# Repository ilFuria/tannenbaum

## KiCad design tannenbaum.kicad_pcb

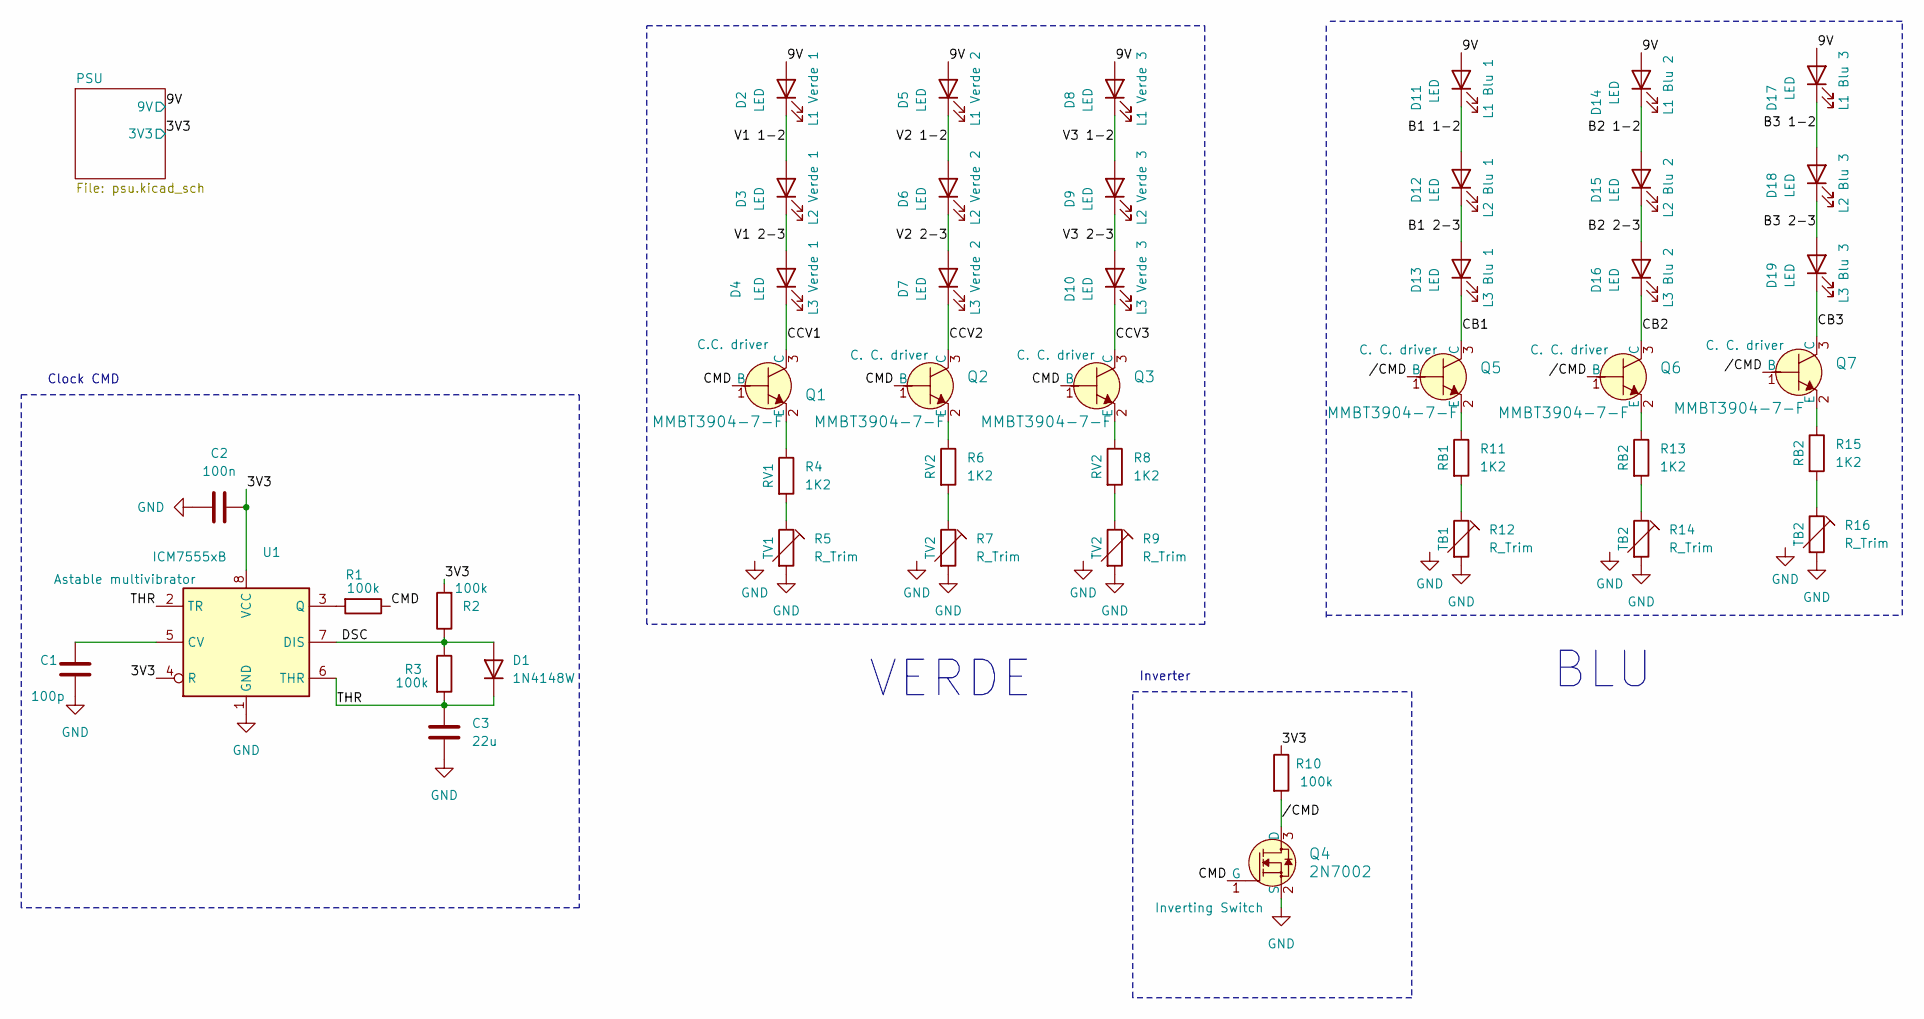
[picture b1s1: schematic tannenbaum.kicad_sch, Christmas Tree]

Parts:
C1: 100p; C_0603_1608Metric
C2: 100n; C_0805_2012Metric
C3: 22u; CP_Elec_6.3x5.7
D1: 1N4148W; D_SOD-123
D2, D3, D4, D5, D6, D7, D8, D9, D10, D11, D12, D13, D14, D15, D16, D17, D18, D19: LED; LED_0805_2012Metric_LW
Q1, Q2, Q3, Q5, Q6, Q7: MMBT3904-7-F; SOT-23-3; MPN MMBT3904-7-F; Digi-Key_PN MMBT3904-FDICT-ND
Q4: 2N7002; SOT-23-3; MPN 2N7002; Digi-Key_PN 2N7002NCT-ND
R1, R2, R3, R10: 100k; R_0805_2012Metric
R4, R6, R8, R11, R13, R15: 1K2; R_0603_1608Metric
R5, R7, R9, R12, R14, R16: R_Trim; Potentiometer_Bourns_TC33X_Vertical
U1: ICM7555xB; SOIC-8_3.9x4.9mm_P1.27mm

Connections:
/3V3: C2.2, R2.2, R10.1, U1.4 (R), U1.8 (VCC); also elsewhere on the board
/9V: D2.2 (A), D5.2 (A), D8.2 (A), D11.2 (A), D14.2 (A), D17.2 (A); also elsewhere on the board
/B1 1-2: D11.1 (K), D12.2 (A)
/B1 2-3: D12.1 (K), D13.2 (A)
/B2 1-2: D14.1 (K), D15.2 (A)
/B2 2-3: D15.1 (K), D16.2 (A)
/B3 1-2: D17.1 (K), D18.2 (A)
/B3 2-3: D18.1 (K), D19.2 (A)
/CB1: D13.1 (K), Q5.3 (C)
/CB2: D16.1 (K), Q6.3 (C)
/CB3: D19.1 (K), Q7.3 (C)
/CCV1: D4.1 (K), Q1.3 (C)
/CCV2: D7.1 (K), Q2.3 (C)
/CCV3: D10.1 (K), Q3.3 (C)
/CMD: Q1.1 (B), Q2.1 (B), Q3.1 (B), Q4.1 (G), R1.1
/DSC: D1.2 (A), R2.1, R3.1, U1.7 (DIS)
/THR: C3.1, D1.1 (K), R3.2, U1.2 (TR), U1.6 (THR)
/V1 1-2: D2.1 (K), D3.2 (A)
/V1 2-3: D3.1 (K), D4.2 (A)
/V2 1-2: D5.1 (K), D6.2 (A)
/V2 2-3: D6.1 (K), D7.2 (A)
/V3 1-2: D8.1 (K), D9.2 (A)
/V3 2-3: D9.1 (K), D10.2 (A)
//CMD: Q4.3 (D), Q5.1 (B), Q6.1 (B), Q7.1 (B), R10.2
GND: C1.2, C2.1, C3.2, Q4.2 (S), R5.2, R5.3, R7.2, R7.3, R9.2, R9.3, R12.2, R12.3, R14.2, R14.3, R16.2, R16.3, U1.1 (GND); also elsewhere on the board
unnamed: Q1.2 (E), R4.1
unnamed: Q2.2 (E), R6.1
unnamed: Q3.2 (E), R8.1
unnamed: Q5.2 (E), R11.1
unnamed: Q6.2 (E), R13.1
unnamed: Q7.2 (E), R15.1
unnamed: R4.2, R5.1
unnamed: R6.2, R7.1
unnamed: R8.2, R9.1
unnamed: R11.2, R12.1
unnamed: R13.2, R14.1
unnamed: R15.2, R16.1
unnamed: C1.1, U1.5 (CV)
unnamed: R1.2, U1.3 (Q)

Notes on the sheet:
Inverter
VERDE
Clock CMD
BLU

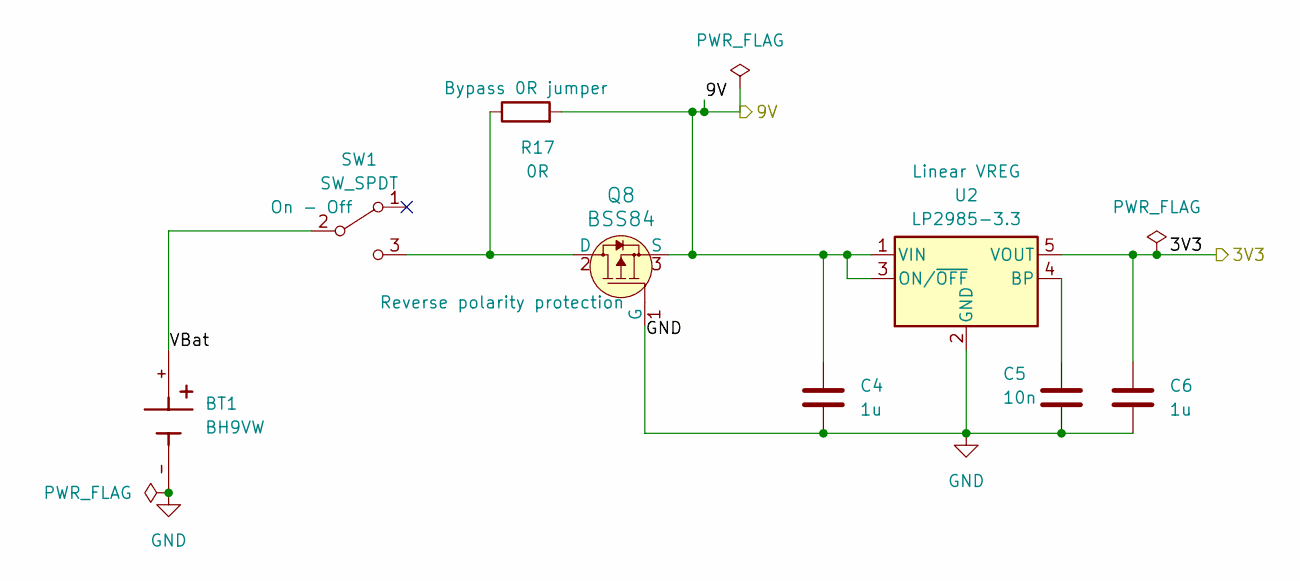
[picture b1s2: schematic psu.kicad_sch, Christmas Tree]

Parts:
BT1: BH9VW; BAT_BH9VW_SMD; PARTREV D; DigiKey_Part_Number BH9VW-ND
C4, C6: 1u; C_0603_1608Metric
C5: 10n; C_0805_2012Metric
Q8: BSS84; SOT-23-3; MPN BSS84; Digi-Key_PN BSS84CT-ND
R17: 0R; R_0805_2012Metric
SW1: SW_SPDT; Switch_Slide_JS202011SCQN
U2: LP2985-3.3; SOT-23-5

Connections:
/3V3: C6.1, U2.5 (VOUT); also elsewhere on the board
/9V: C4.1, Q8.3 (S), R17.2, U2.1 (VIN), U2.3 (ON/~OFF); also elsewhere on the board
/PSU/VBat: BT1.+, SW1.2 (B)
GND: BT1.-, C4.2, C5.2, C6.2, Q8.1 (G), U2.2 (GND); also elsewhere on the board
unnamed: Q8.2 (D), R17.1, SW1.3 (C)
unnamed: C5.1, U2.4 (BP)

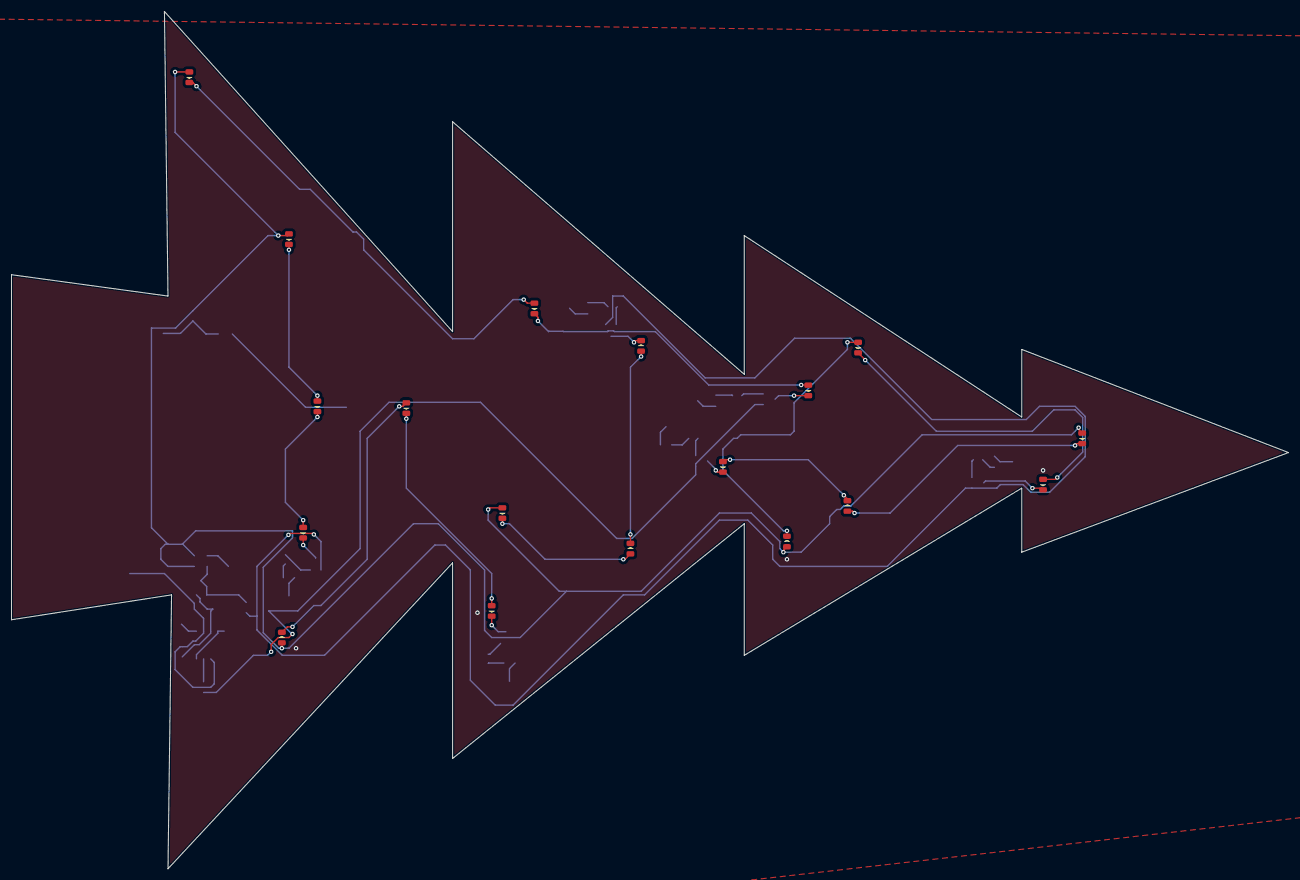
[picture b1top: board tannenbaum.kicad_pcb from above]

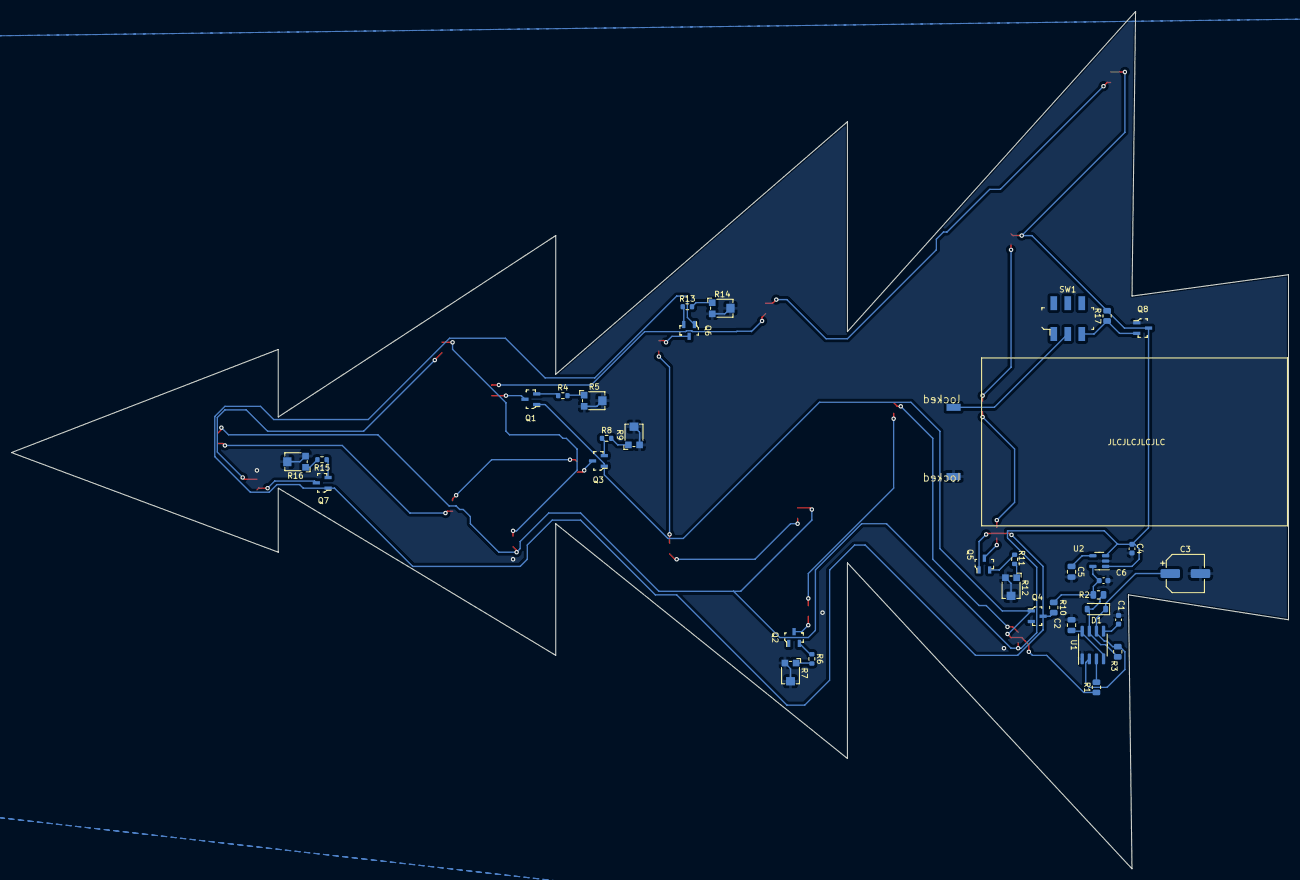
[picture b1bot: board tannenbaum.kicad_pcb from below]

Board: 2 copper layers, 228.0 x 153.0 mm, 54 parts (36 on the bottom side), 42 nets.

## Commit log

2023-08-19 Init
2023-08-19 setup
2023-08-19 batt
2023-08-19 predr
2023-08-19 grigila
2023-08-20 nuovo regolatore
2023-08-20 gitignore e revised sch
2023-08-20 verzion
2023-08-20 estetica
2023-08-20 nets
2023-08-20 trims
2023-08-21 corretti simboli
2023-08-22 corretti impronte
2023-08-22 gerber
2023-08-28 finish
